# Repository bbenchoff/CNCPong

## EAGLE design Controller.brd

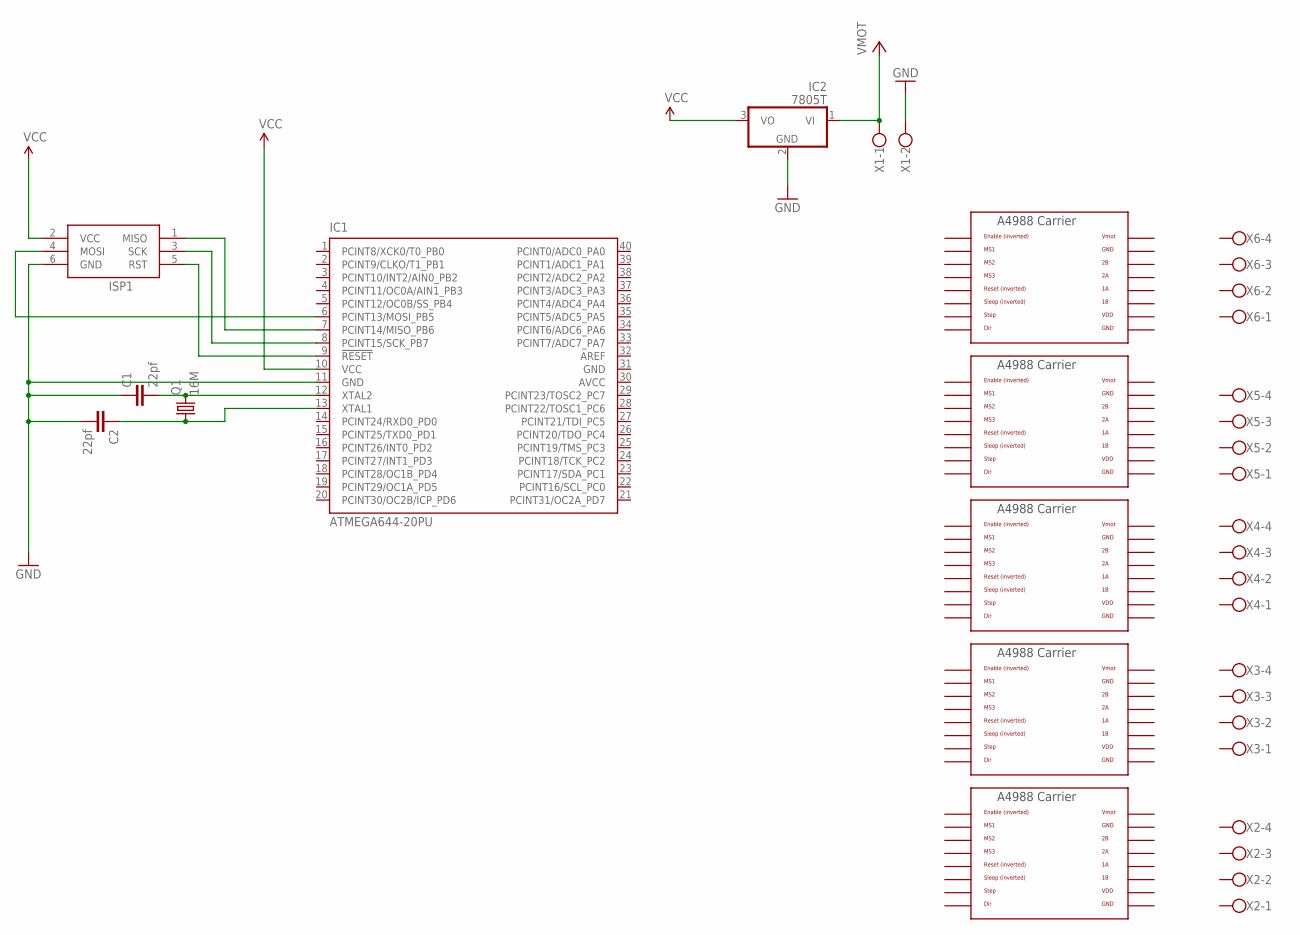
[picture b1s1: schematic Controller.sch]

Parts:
C1, C2: 22pf; CAP-PTH-SMALL
IC1: ATMEGA644-20PU; DIL40
IC2: 7805T; TO220H
ISP1: AVRISP-6; AVRISP
Q1: 16M; HC49U-V
U$1, U$2, U$3, U$4, U$5: A4988BREAKOUT
X1: W237-102
X2, X3, X4, X5, X6: W237-4

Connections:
AVCC: IC1.30 (AVCC)
GND: C1.1, C2.2, IC1.11 (GND), IC1.31 (GND), IC2.2 (GND), ISP1.6 (GND), U$1.GND, U$1.GND@0 (GND), U$2.GND, U$2.GND@0 (GND), U$3.GND, U$3.GND@0 (GND), U$4.GND, U$4.GND@0 (GND), U$5.GND, U$5.GND@0 (GND), X1.2
unnamed: IC1.8 (PCINT15/SCK_PB7), ISP1.3 (SCK)
unnamed: IC1.9 (!RESET), ISP1.5 (RST)
unnamed: IC1.7 (PCINT14/MISO_PB6), ISP1.1 (MISO)
unnamed: IC1.6 (PCINT13/MOSI_PB5), ISP1.4 (MOSI)
unnamed: IC2.1 (VI), X1.1
unnamed: C1.2, IC1.12 (XTAL2), Q1.2
unnamed: C2.1, IC1.13 (XTAL1), Q1.1
VCC: IC1.10 (VCC), IC2.3 (VO), ISP1.2 (VCC)
VDD: U$1.VDD, U$2.VDD, U$3.VDD, U$4.VDD, U$5.VDD
VMOT: U$1.VMOT, U$2.VMOT, U$3.VMOT, U$4.VMOT, U$5.VMOT

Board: 2 copper layers, 17 parts (0 on the bottom side), 11 nets, no tracks yet.

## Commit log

2016-06-19 :confetti_ball: Added .gitattributes & .gitignore files
2016-06-19 board

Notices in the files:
parts and their libraries:
SparkFun-Capacitors: Licensing: Creative Commons ShareAlike 4.0 International - https://creativecommons.org/licenses/by-sa/4.0
